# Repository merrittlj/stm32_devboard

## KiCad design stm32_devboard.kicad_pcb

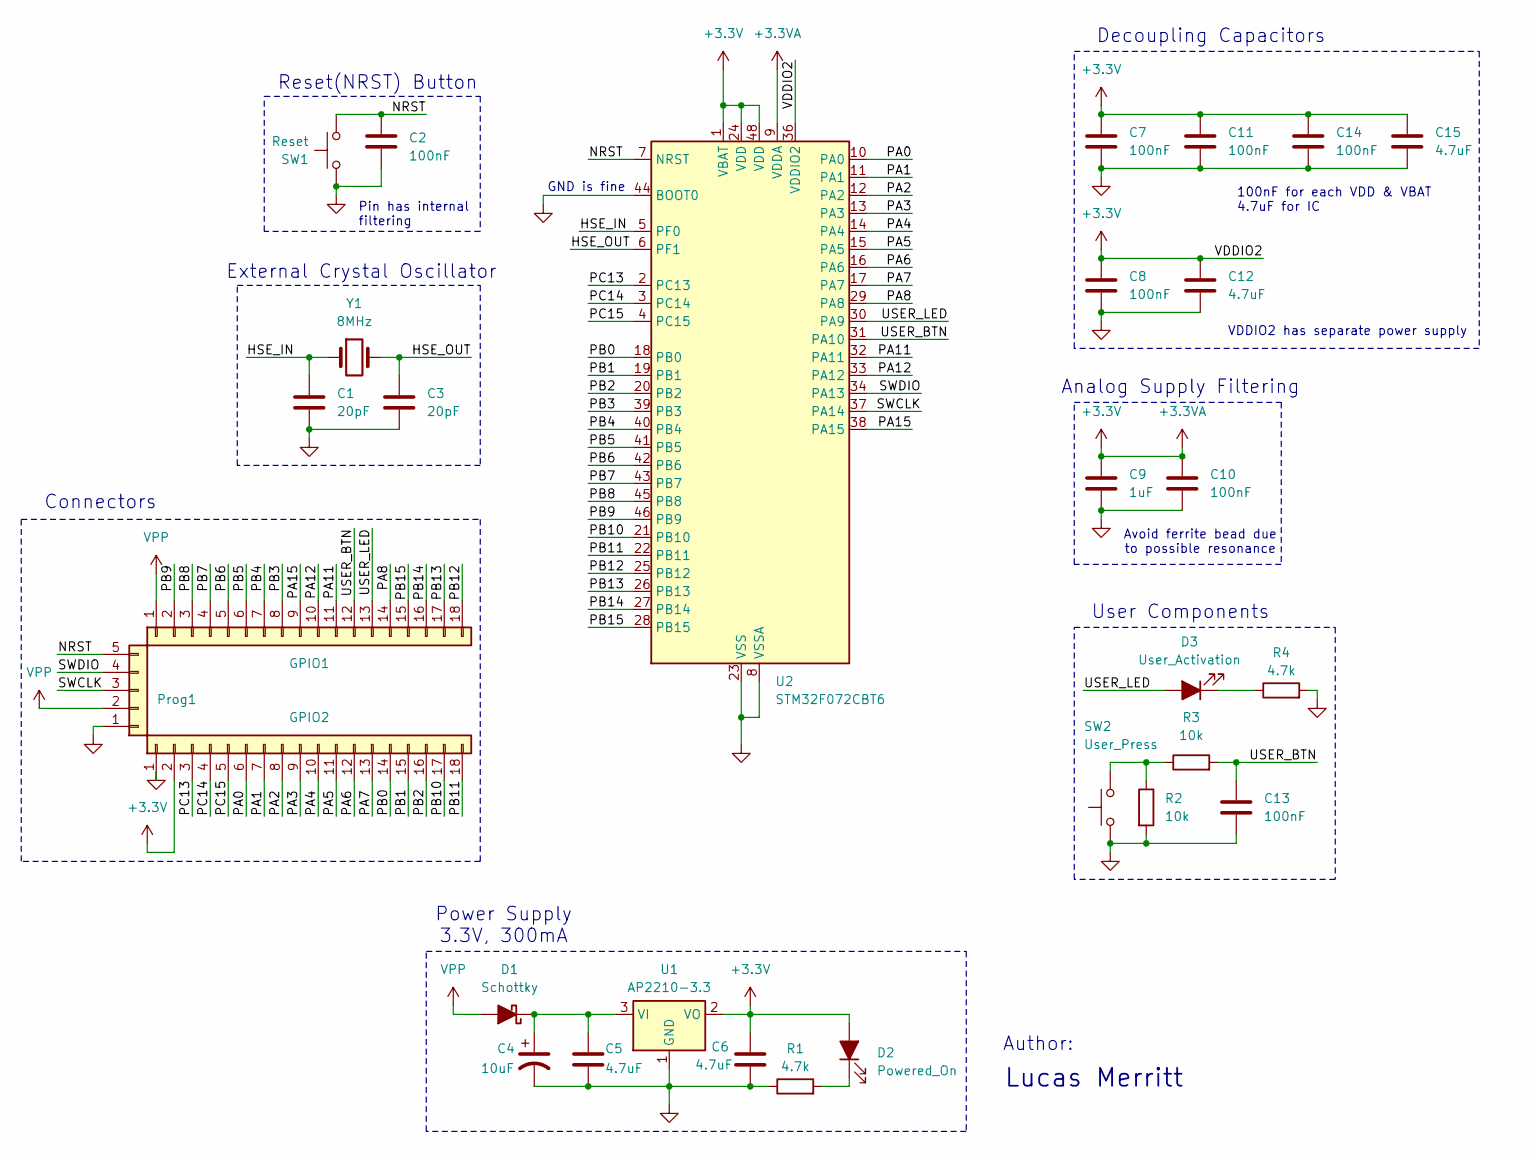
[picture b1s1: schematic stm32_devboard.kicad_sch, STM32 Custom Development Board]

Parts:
C1, C3: 20pF; C_0805_2012Metric_Pad1.18x1.45mm_HandSolder
C2, C7, C8, C10, C11, C13, C14: 100nF; C_0805_2012Metric_Pad1.18x1.45mm_HandSolder
C4: 10uF; C_1206_3216Metric_Pad1.33x1.80mm_HandSolder
C5, C6, C12, C15: 4.7uF; C_0805_2012Metric_Pad1.18x1.45mm_HandSolder
C9: 1uF; C_0805_2012Metric_Pad1.18x1.45mm_HandSolder
D1: Schottky; D_SOD-123
D2: Powered_On; LED_0805_2012Metric_Pad1.15x1.40mm_HandSolder
D3: User_Activation; LED_0805_2012Metric_Pad1.15x1.40mm_HandSolder
GPIO1, GPIO2: Conn_01x18; PinHeader_1x18_P2.54mm_Vertical
Prog1: Conn_01x05; PinHeader_1x05_P2.54mm_Horizontal
R1, R4: 4.7k; R_0805_2012Metric_Pad1.20x1.40mm_HandSolder
R2, R3: 10k; R_0805_2012Metric_Pad1.20x1.40mm_HandSolder
SW1: Reset; SW_Push_1P1T_NO_6x6mm_H9.5mm
SW2: User_Press; SW_Push_1P1T_NO_6x6mm_H9.5mm
U1: AP2210-3.3; SOT-23-3
U2: STM32F072CBT6; LQFP-48_7x7mm_P0.5mm
Y1: 8MHz; Crystal_SMD_Abracon_ABM3-2Pin_5.0x3.2mm_HandSoldering

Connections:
+3.3V: C6.1, C7.1, C8.1, C9.1, C10.1, C11.1, C12.1, C14.1, C15.1, D2.2 (A), GPIO2.2, U1.2 (VO), U2.1 (VBAT), U2.9 (VDDA), U2.24 (VDD), U2.36 (VDDIO2), U2.48 (VDD)
/HSE_IN: C1.1, U2.5 (PF0), Y1.1
/HSE_OUT: C3.1, U2.6 (PF1), Y1.2
/NRST: C2.1, Prog1.5, SW1.2, U2.7 (NRST)
/PA0: GPIO2.6, U2.10 (PA0)
/PA1: GPIO2.7, U2.11 (PA1)
/PA2: GPIO2.8, U2.12 (PA2)
/PA3: GPIO2.9, U2.13 (PA3)
/PA4: GPIO2.10, U2.14 (PA4)
/PA5: GPIO2.11, U2.15 (PA5)
/PA6: GPIO2.12, U2.16 (PA6)
/PA7: GPIO2.13, U2.17 (PA7)
/PA8: GPIO1.14, U2.29 (PA8)
/PA11: GPIO1.11, U2.32 (PA11)
/PA12: GPIO1.10, U2.33 (PA12)
/PA15: GPIO1.9, U2.38 (PA15)
/PB0: GPIO2.14, U2.18 (PB0)
/PB1: GPIO2.15, U2.19 (PB1)
/PB2: GPIO2.16, U2.20 (PB2)
/PB3: GPIO1.8, U2.39 (PB3)
/PB4: GPIO1.7, U2.40 (PB4)
/PB5: GPIO1.6, U2.41 (PB5)
/PB6: GPIO1.5, U2.42 (PB6)
/PB7: GPIO1.4, U2.43 (PB7)
/PB8: GPIO1.3, U2.45 (PB8)
/PB9: GPIO1.2, U2.46 (PB9)
/PB10: GPIO2.17, U2.21 (PB10)
/PB11: GPIO2.18, U2.22 (PB11)
/PB12: GPIO1.18, U2.25 (PB12)
/PB13: GPIO1.17, U2.26 (PB13)
/PB14: GPIO1.16, U2.27 (PB14)
/PB15: GPIO1.15, U2.28 (PB15)
/PC13: GPIO2.3, U2.2 (PC13)
/PC14: GPIO2.4, U2.3 (PC14)
/PC15: GPIO2.5, U2.4 (PC15)
/SWCLK: Prog1.3, U2.37 (PA14)
/SWDIO: Prog1.4, U2.34 (PA13)
/USER_BTN: C13.1, GPIO1.12, R3.2, U2.31 (PA10)
/USER_LED: D3.2 (A), GPIO1.13, U2.30 (PA9)
GND: C1.2, C2.2, C3.2, C4.2, C5.2, C6.2, C7.2, C8.2, C9.2, C10.2, C11.2, C12.2, C13.2, C14.2, C15.2, GPIO2.1, Prog1.1, R1.1, R2.2, R4.2, SW1.1, SW2.1, U1.1 (GND), U2.8 (VSSA), U2.23 (VSS), U2.35 (VSS), U2.44 (BOOT0), U2.47 (VSS)
unnamed: C4.1, C5.1, D1.1 (K), U1.3 (VI)
unnamed: D2.1 (K), R1.2
unnamed: D3.1 (K), R4.1
unnamed: R2.1, R3.1, SW2.2
VPP: D1.2 (A), GPIO1.1, Prog1.2

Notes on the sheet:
100nF for each VDD & VBAT 4.7uF for IC
Power Supply 3.3V, 300mA
Connectors
Decoupling Capacitors
Lucas Merritt
Avoid ferrite bead due to possible resonance
VDDIO2 has separate power supply
External Crystal Oscillator
Pin has internal filtering
User Components
Reset(NRST) Button
Author:
Analog Supply Filtering
GND is fine

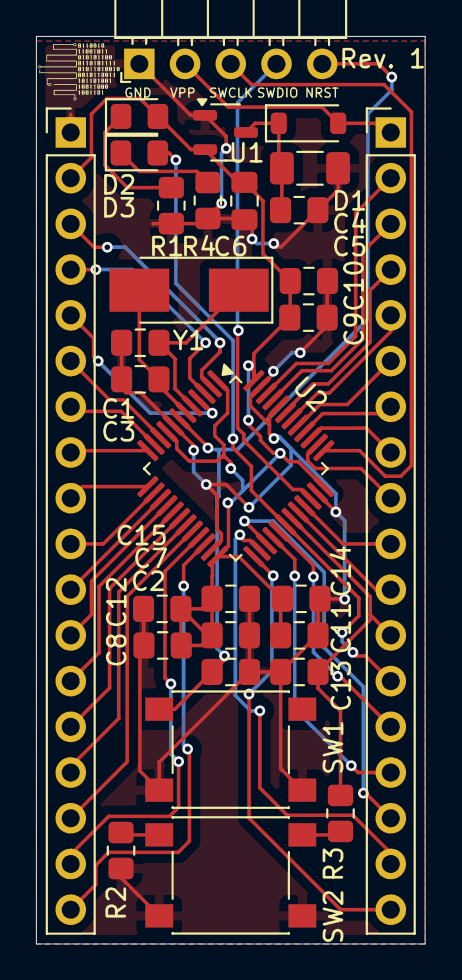
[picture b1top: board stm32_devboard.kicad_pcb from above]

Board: 2 copper layers, 21.6 x 50.4 mm, 30 parts (0 on the bottom side), 45 nets.

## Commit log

2024-05-31 schematic done: errors not yet corrected
2024-06-02 Schematic Rev. 2: Fix all errors, finalized version for PCB
2024-06-19 PCB/schematic updates
2024-07-17 Add new footprints
2024-07-17 update pcb from schem
2024-07-23 pcb work
2024-07-28 PCB rev 1
2024-07-28 update schem
2024-07-28 rev1
